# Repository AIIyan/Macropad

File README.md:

# Macropad
 Design of a macropad using an arduino pro micro

 current issues:
 - display needs to be moved down and to the left so it is not in the way of the other components
 - rotary encoders need to be rerouted to interrupt pins

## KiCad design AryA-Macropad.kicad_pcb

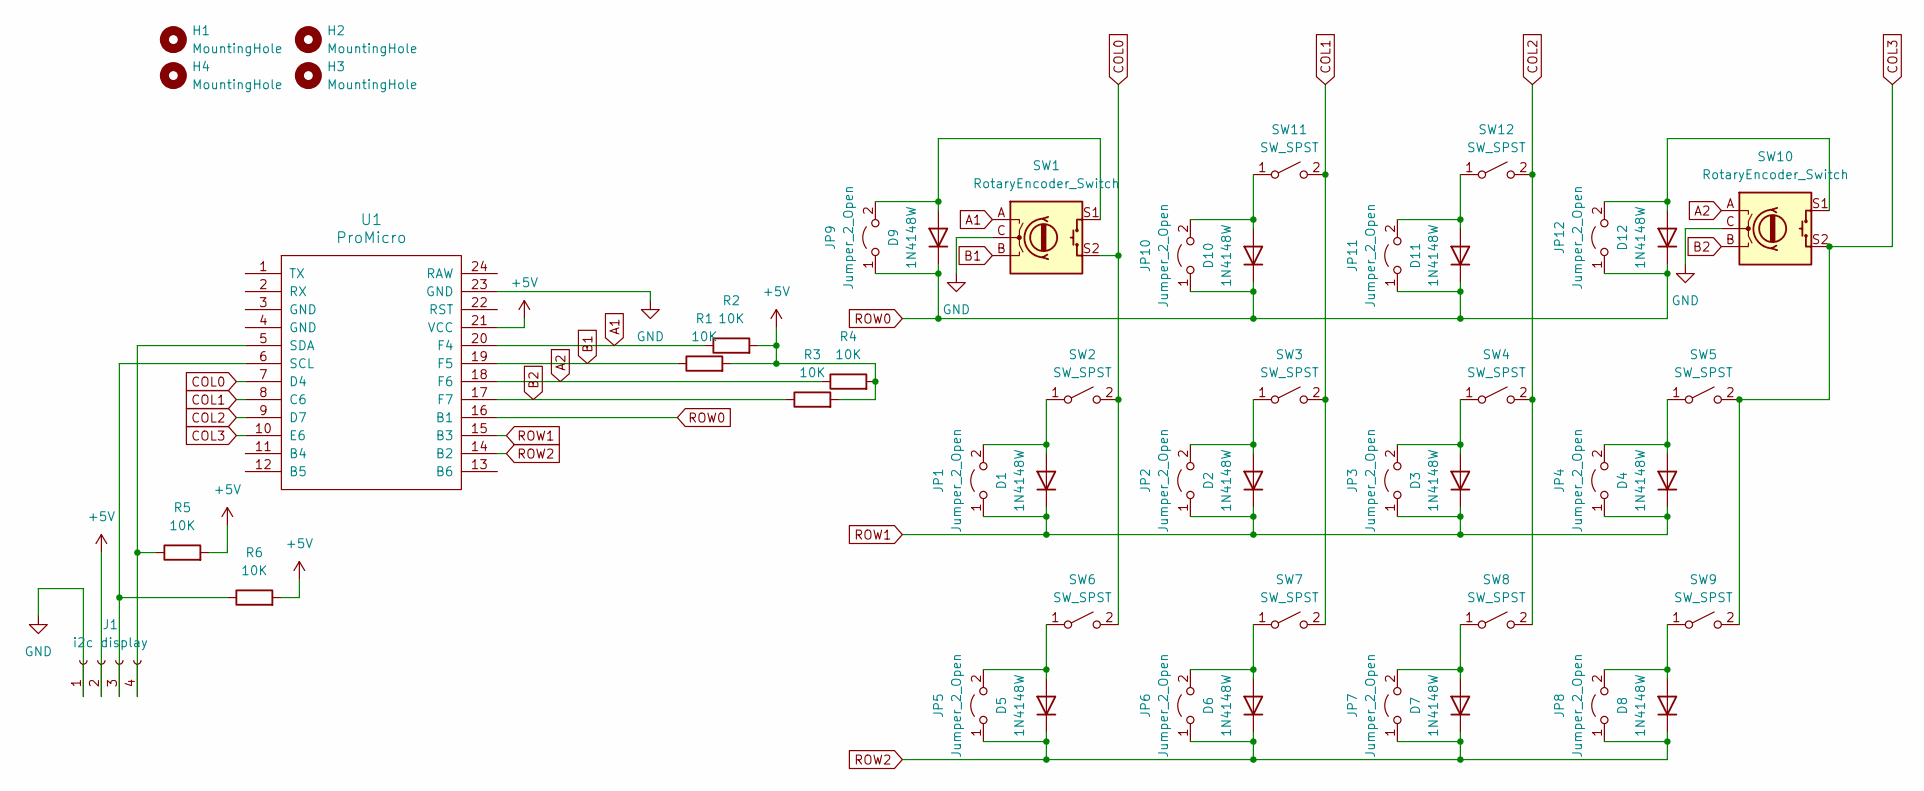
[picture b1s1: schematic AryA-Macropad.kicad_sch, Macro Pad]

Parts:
D1, D2, D3, D4, D5, D6, D7, D8, D9, D10, D11, D12: 1N4148W; D_SOD-123
H1, H2, H3, H4: MountingHole; MountingHole_2.5mm
J1: i2c display; PinHeader_1x04_P2.54mm_Vertical
JP1, JP2, JP3, JP4, JP5, JP6, JP7, JP8, JP9, JP10, JP11, JP12: Jumper_2_Open; SolderJumper-2_P1.3mm_Bridged_Pad1.0x1.5mm
R1, R2, R3, R4, R5, R6: 10K; R_1206_3216Metric_Pad1.30x1.75mm_HandSolder
SW1, SW10: RotaryEncoder_Switch; RotaryEncoder_Alps_EC11E-Switch_Vertical_H20mm_CircularMoun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
SW2, SW3, SW4, SW5, SW6, SW7, SW8, SW9, SW11, SW12: SW_SPST; SW_Cherry_MX_PCB_1.00u
U1: ProMicro

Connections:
+5V: J1.2, R1.2, R2.2, R3.2, R4.2, R5.2, R6.2, U1.21 (VCC)
A1: R2.1, SW1.A, U1.20 (F4)
A2: R4.1, SW10.A, U1.18 (F6)
B1: R1.1, SW1.B, U1.19 (F5)
B2: R3.1, SW10.B, U1.17 (F7)
COL0: SW1.S2, SW2.2 (B), SW6.2 (B), U1.7 (D4)
COL1: SW3.2 (B), SW7.2 (B), SW11.2 (B), U1.8 (C6)
COL2: SW4.2 (B), SW8.2 (B), SW12.2 (B), U1.9 (D7)
COL3: SW5.2 (B), SW9.2 (B), SW10.S2, U1.10 (E6)
GND: J1.1, SW1.C, SW10.C, U1.23 (GND)
unnamed: D1.2 (A), JP1.2 (B), SW2.1 (A)
unnamed: D2.2 (A), JP2.2 (B), SW3.1 (A)
unnamed: D3.2 (A), JP3.2 (B), SW4.1 (A)
unnamed: D4.2 (A), JP4.2 (B), SW5.1 (A)
unnamed: D5.2 (A), JP5.2 (B), SW6.1 (A)
unnamed: D6.2 (A), JP6.2 (B), SW7.1 (A)
unnamed: D7.2 (A), JP7.2 (B), SW8.1 (A)
unnamed: D8.2 (A), JP8.2 (B), SW9.1 (A)
unnamed: D9.2 (A), JP9.2 (B), SW1.S1
unnamed: D10.2 (A), JP10.2 (B), SW11.1 (A)
unnamed: D11.2 (A), JP11.2 (B), SW12.1 (A)
unnamed: D12.2 (A), JP12.2 (B), SW10.S1
unnamed: J1.3, R6.1, U1.6 (SCL)
unnamed: J1.4, R5.1, U1.5 (SDA)
ROW0: D9.1 (K), D10.1 (K), D11.1 (K), D12.1 (K), JP9.1 (A), JP10.1 (A), JP11.1 (A), JP12.1 (A), U1.16 (B1)
ROW1: D1.1 (K), D2.1 (K), D3.1 (K), D4.1 (K), JP1.1 (A), JP2.1 (A), JP3.1 (A), JP4.1 (A), U1.15 (B3)
ROW2: D5.1 (K), D6.1 (K), D7.1 (K), D8.1 (K), JP5.1 (A), JP6.1 (A), JP7.1 (A), JP8.1 (A), U1.14 (B2)

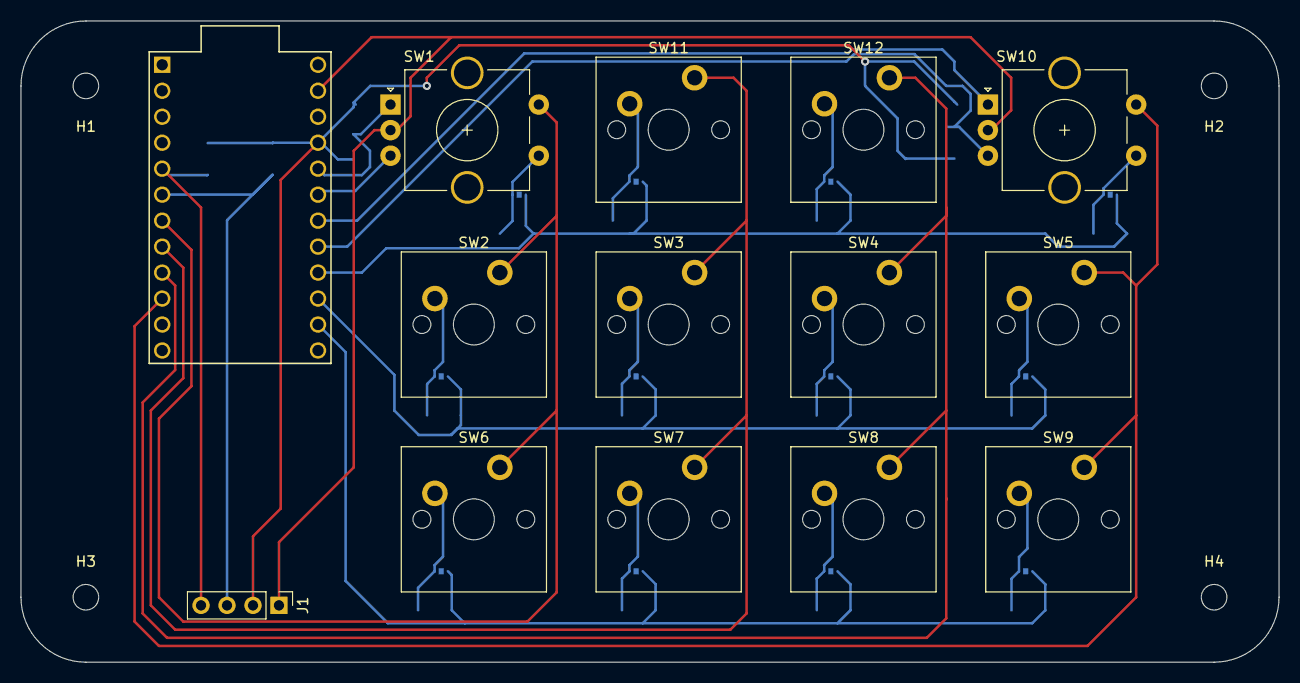
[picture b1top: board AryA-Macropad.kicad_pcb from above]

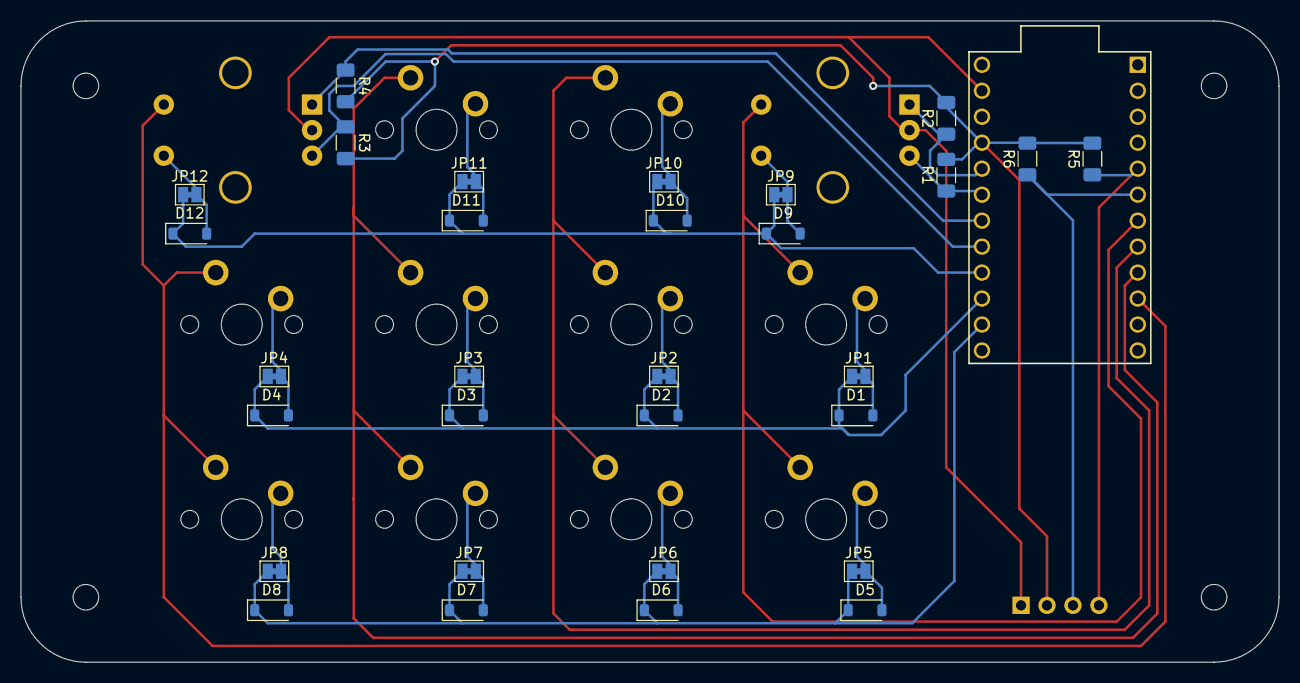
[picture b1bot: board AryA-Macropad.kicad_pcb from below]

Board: 2 copper layers, 123.0 x 62.7 mm, 48 parts (30 on the bottom side), 27 nets.

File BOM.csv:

"Id";"Designator";"Footprint";"Quantity";"Designation";"Supplier and ref";
1;"SW11,SW8,SW4,SW2,SW5,SW9,SW3,SW6,SW7,SW12";"SW_Cherry_MX_PCB_1.00u";10;"SW_SPST";;;
2;"J1";"PinHeader_1x04_P2.54mm_Vertical";1;"i2c display";;;
3;"H1,H2,H3,H4";"MountingHole_2.5mm";4;"MountingHole";;;
4;"U1";"ProMicro";1;"ProMicro";;;
5;"SW1,SW10";"RotaryEncoder_Alps_EC11E-Switch_Vertical_H20mm_CircularMountingHoles";2;"RotaryEncoder_Switch";;;
6;"R3,R2,R5,R6,R4,R1";"R_1206_3216Metric_Pad1.30x1.75mm_HandSolder";6;"10K";;;
7;"D7,D11,D6,D9,D3,D5,D4,D10,D1,D2,D12,D8";"D_SOD-123";12;"1N4148W";;;
8;"JP6,JP1,JP12,JP8,JP10,JP3,JP9,JP2,JP5,JP7,JP4,JP11";"SolderJumper-2_P1.3mm_Bridged_Pad1.0x1.5mm";12;"Jumper_2_Open";;;

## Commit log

2024-01-09 KiCAD Project
    Created a KiCAD project design
2024-01-09 add submodules
2024-01-09 added libraries to project
2024-01-09 initial schematic and pcb designed
2024-01-13 Wiring everything up
2024-01-14 finishing up schematic
2024-01-15 1.0 complete
2024-01-24 updated code
2024-01-25 added 3d models
2024-01-25 step file generated
2024-01-26 small changes
2024-01-31 various post manufactring adjustme
